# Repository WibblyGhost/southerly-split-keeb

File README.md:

# The Southerly - Split Keeb

**Brrrr is it cold down here in New Zealand winters!**

## Intro

In 2024 I was getting some serious wrist pain issues from typing all day at my job as a programmer, so I ventured into the world of split keyboards.

Initially I was just curious, but as time went on I really enjoyed the idea of having two keyboard halves an was quite keen on the staggered column. This quickly turned into a purchase of my first split keyboard, the [ZSA Voyager](https://www.zsa.io/voyager). I quickly fell in love with the keyboard and how it felt with my hands.
Alongside also purchasing a Logitech MX Ergo trackball mouse.

I had quite a tough learning experience to switching to the Voyager strictly due to the fact that whilst I changed keyboard layouts, I switched from traditional mice to trackball mice, **and** started learning the ColemakDH keyboard layout.

Switching to the new layer system, getting rid of the numpad, F-keys, moving spaces, tabs and enters; whilst incredibly fun, was quite intensive switch over. But now sitting here a few months after my mission to improve desk ergonomics; I'm feeling a hell of a lot better with all my pain, voila, gone!

## Layout Printouts/Design - ErgoGen

I came across ErgoGen when researching about split keyboards, this piece of software is marvelous... complex but marvelous. It took me quite a while to figure out how to use ErgoGen and their official docs are still a WIP meaning I was initially going blind with this software.

I came across this youtube video [ErgoGen Tutorial](https://www.youtube.com/watch?v=7UXsD7nSfDY) which dramatically helped me start with the design of my keyboard.

Another great guide I came across was this one, which in my honest opinion, **is the best ErgoGen doc set I have found to date**; [ErgoGen Full Guide](https://flatfootfox.com/ergogen-part1-units-points/)

As an initial design process I decided to create a few models, drill holes and tried them out on my fingers. With my owned Voyager, I was able to replicate quite easily the positioning I wanted all the keys in, with the addition of a couple more thumb keys.

There was going to be three layers to the case design which I'll get into later. But the brief is a bottom plate which becomes the surrounding case, a top plate which sits just under the switches (they click into the top layer) and the circuit board which will be centered below the top layer by a few millimeters.

### Prototyping

I made **lots** of prototypes for my board as I went through multiple designs. Starting with a basic layout to see what worked well with my hands with the original Voyager as reference.

## PCB Design - KiCad

Once I sorted out the prototyping of the board I moved on to the wiring of the circuit board. The PCB was designed with the idea of being reversible, meaning you can mount the components either way, *but there was a caveat there*.

The PCB design was fairly straightforward running the horizontal traces on one layer and vertical traces on the other, with an addition of two ground planes and thicker VCC/GND traces. The only annoying thing was that KiCad, for the life of me, doesn't support angle snapping at strange angles; and my thumb cluster is on a 30° angle. Making the thumb cluster super messy. Sigh...

The RGB data in and data out connectors were not a part of the schematic so I had to use a third party plugin to help me modify the web and attach the string of LED's to one of the PCB's pinouts. [WireIt](https://github.com/devbisme/WireIt)

After designing the PCB I shipped the Gerber off to JLCPBC to print off for me.

### PCB Underside - LH

### PCB Topside - LH

## Gotcha Moment

Although once receiving the board I realized that the reversible board wouldn't work with the ProMicro the way I had designed it for the 3D design plan as I wanted a minimal keyboard with little height. For that I would have needed to mount MCU directly on the circuit board. So that's a consideration for my next build.

Since my board was already designed to be flippable, the only thing I needed to change was the MCU, so I flipped the MCU footprint and re-traced everything again for the right handed layout.

### PCB Underside - RH

### PCB Topside - RH

## Case Design - AutoDesk Fusion

Whilst ErgoGen can and does generate most 3D print designs and DXF files, I found it quite fiddly changing the YAML constantly to design a case.

So instead I decided that the best course was to get a rough outline in ErgoGen, then work the rest of the design in AutoDesk. The ErgoGen created some annoying fillets in the output, so I removed those and re-created the fillets to clean up the design.

### Upper Case

This was fairly straightforward as I just imported the base outlines created from ErgoGen as sketches and worked on them from there.

From the sketches I firstly designed the upper case which was designed to clip into a base.

Using the sketch outputs I was able to create the Choc V1 socket holes, added key cap pullers to them, and a rectangular cutout underneath to allow the switched to clip into the case properly.

The addition of the reset switch, TRRS and USB-C cutouts was straightforward, just an easy sketch and a subtraction extrude.

Additional fun logo was embossed onto the case too.

> [!NOTE]
> Total thickness of the area between the top plate and rectangular cutout must be exactly 14mm for the switches to properly click in, this was giving me some grief with our 3D printer, we set infill to 100% to prevent any wavey patterns around the switches, and waited until the 3D print bed completely cooled. Otherwise the switch holes shrunk due to rapid cooling or warping.
>
> Also, the TRRS cutout needed a 'brim ears' underneath to prevent liftoff from the base plate during printing.

### Lower Case

From the sketches I designed a lower case, or base, which will support an upper case and fit snugly together. This was done by creating inner walls which extruded into the top layer *(subtraction)* to the fit, and a hex fill for supporting the PCB, *which I also added some foam in for sound proofing and support*.

Adding in a patterned hex structure to the inside to help support the PCB. I added some foam on top of this to fill in the spaces, provide more support, and sound proofing.

### Standoffs

I made some simple standoff feet to tent the keyboard and am using rubber to help prevent the keyboard from moving on the desk. It can be attached via a M5 screw and washer pair and the rubber layer either glued of clipped into the standoff base. I used PLA for the base of the standoff and TPU rubber for the foot.

### Combined Output

## QMK Firmware

QMK was an interesting beast to try learn and it took me a lot of trial and error figuring out how to program the keyboard. I'm still confused on what the right way to define the parameters are, we have the legacy solution, C header files, C files and rules makefiles, or data driven files with JSON which is the new format. However the documentation isn't really up to date with the new JSON format and the C files also lacked up to date documentation.

There were other keyboards in the repository that I had to copy and paste to see what worked and what didn't.

The pinouts of the ProMicro was a bit confusing at first as they didn't match what was on the MCU physically; once I found this image I was able to map the pins correctly to the PCB design. Now correctly mapping the columns and rows, and RGB matrix.

Also found it quite handy that I was able to download the source QMK firmware for the Voyager and reverse engineer the QMK setup for the Voyager. This allowed me to understand the QMK design process better and how the matrices are used. Also means that I could take a layout I made for my Voyager and with the addition of the extra thumb buttons and removal of some unnecessary functions, was able to get a running board very quickly.

## Components

| Components | ID | Links | Total Cost (NZD) | Quantity | Notes |
| ---------- | -- | ----- | ---------- | -------- | ----- |
| Choc V1 Keycaps | | [Tai-Hao Thins](https://shop.tai-hao.com/products/white-1) | $96.67 | | Same key caps as ZSA Voyager (Needs to be double injected for the RGB) |
| Choc V1 Switches | | [Robins](https://keebd.com/en-nz/products/ambients-silent-linear-twilight-choc-switches?_pos=2&_fid=9a770a5f9&_ss=c) | $60 | 60 | |
| Kailh Hotswap Sockets | | [Choc Hotswap Sockets](https://www.aliexpress.com/item/1005006833673668.html) | $24 | 60 | |
| Pico Micro (USB-C) | | [AliExpress](https://www.aliexpress.com/item/1576902211.html) | $13.7 | 2 | |
| Surface Mount Diodes | SOD 123 - DSF1J | [LCSC](https://www.lcsc.com/product-detail/Fast-Recovery-High-Efficiency-Diodes_FUXINSEMI-DSF1J_C915615.html) | $1.58 | 200 | |
| RGB | led_sk6812mini-e | [LCSC](https://www.lcsc.com/product-detail/RGB-LEDs-Built-in-IC_OPSCO-Optoelectronics-SK6812MINI-E_C5149201.html) | $7.15 | 100 | |
| Surface Mount Reset Button | EVQPUA02K | [LCSC](https://www.lcsc.com/product-detail/Tactile-Switches_PANASONIC-EVQPUA02K_C128539.html) | $1.62 | 5 | |
| TRRS Connector | PJ-320A | [LCSC](https://www.lcsc.com/product-detail/Audio-Connectors_XKB-Connectivity-PJ-320AG-B_C2884984.html) | $0.39 | 5 | |
| TRRS Cable | UGREEN 20782 | [PB Tech](https://www.pbtech.co.nz/product/CABUGR6192/UGREEN-20782-35mm-Male-To-Male-Cable---2M) | $20 | 5 | **You need a 4 pole TRRS cable** (I struggled finding one so just ordered one locally) |
| Circuit Board | | [JLCPCB](https://jlcpcb.com/) | $11.76 | 5 | |
| **Total** | | | **$236.87** | | |

## Notes

- The key caps **must** be double injected for the RGB to shine through, otherwise you will just get an under-glow.

### ErgoGen

- [ErgoGen Guide - Units & Points](https://flatfootfox.com/ergogen-part1-units-points/)
- [YouTube Guide - Designing and Building a Split Keyboard](https://www.youtube.com/watch?v=7UXsD7nSfDY)
- [Notion Guide - Convert KiCad to ErgoGen Footprints](https://nilnil.notion.site/Convert-Kicad-Footprints-to-Ergogen-8340ce87ad554c69af4e3f92bc9a0898)
- [ErgoGen Footprints](https://github.com/ceoloide/ergogen-footprints/tree/main)

### PCB

- [PCB Addon - Wire RatsNest](https://github.com/devbisme/WireIt)
- [PCB Printing - JLCPCB](https://jlcpcb.com/)

### QMK

- [QMK Bootloader](https://docs.qmk.fm/driver_installation_zadig#list-of-known-bootloaders)
- [QMK Matrix to Physical Layout Map](https://docs.qmk.fm/understanding_qmk#matrix-to-physical-layout-map)
- [VSCode Setup](https://docs.qmk.fm/other_vscode)
- Split Keyboard
  - [Serial Wiring](https://docs.qmk.fm/features/split_keyboard#serial-wiring)
  - [Split Keyboard](https://docs.qmk.fm/features/split_keyboard#split-keyboard)
  - [Keeb Handedness](https://docs.qmk.fm/features/split_keyboard#handedness-by-eeprom)
- RGB
  - [RGB: WS2812 LED](https://docs.qmk.fm/drivers/ws2812)
  - [RGB: Matrix](https://docs.qmk.fm/features/rgb_matrix)
- TRRS
  - [TRRS: I2C](https://docs.qmk.fm/drivers/i2c)
  - [TRRS: Serial](https://docs.qmk.fm/drivers/serial)
- Data Driven Configs (.json) - New
  - [QMK JSON (.json) - Preferred Way](https://docs.qmk.fm/reference_info_json)
  - [QMK Data Driven Config](https://docs.qmk.fm/data_driven_config)
- Header Configs (.h/.mk) - Legacy
  - [QMK Config.h](https://docs.qmk.fm/config_options#the-configh-file)
  - [QMK Rules.mk](https://docs.qmk.fm/config_options#the-rules-mk-file)

<!-- TODO: qmk flash -kb southerly -km default -bl avsdude-split-left -->

## Improvements & Considerations

- Next time instead of using a Pro Micro, I will use a MEGA32U4 directly on the board and design the components directly into the board.
  > This will cleanup the USB-C port location and make the reversible board work correctly without having to re-design the PCB case for the mirrored side.

- Diagnose why a TRRS port isn't compatible with a TRS cable *(common audio cable)*, it must use a TRRS cable instead *(4 Pole audio cable)*.
  > I had troubles when first trying this out with a TRS cable and it shorted VCC to GND, the MCU never booted whilst plugged into TRRS.

- Use I2C for TRRS communications next time, this requires some rewiring on the PCB with some pull up resistors. But will allow for multiple devices to be connected through TRRS.

- Figure out how to do matrix lighting from master to slave. (It's doesn't seem to want to update the slave correctly)

- Figure out how the master slave connection works properly, allow USB connection from either side?

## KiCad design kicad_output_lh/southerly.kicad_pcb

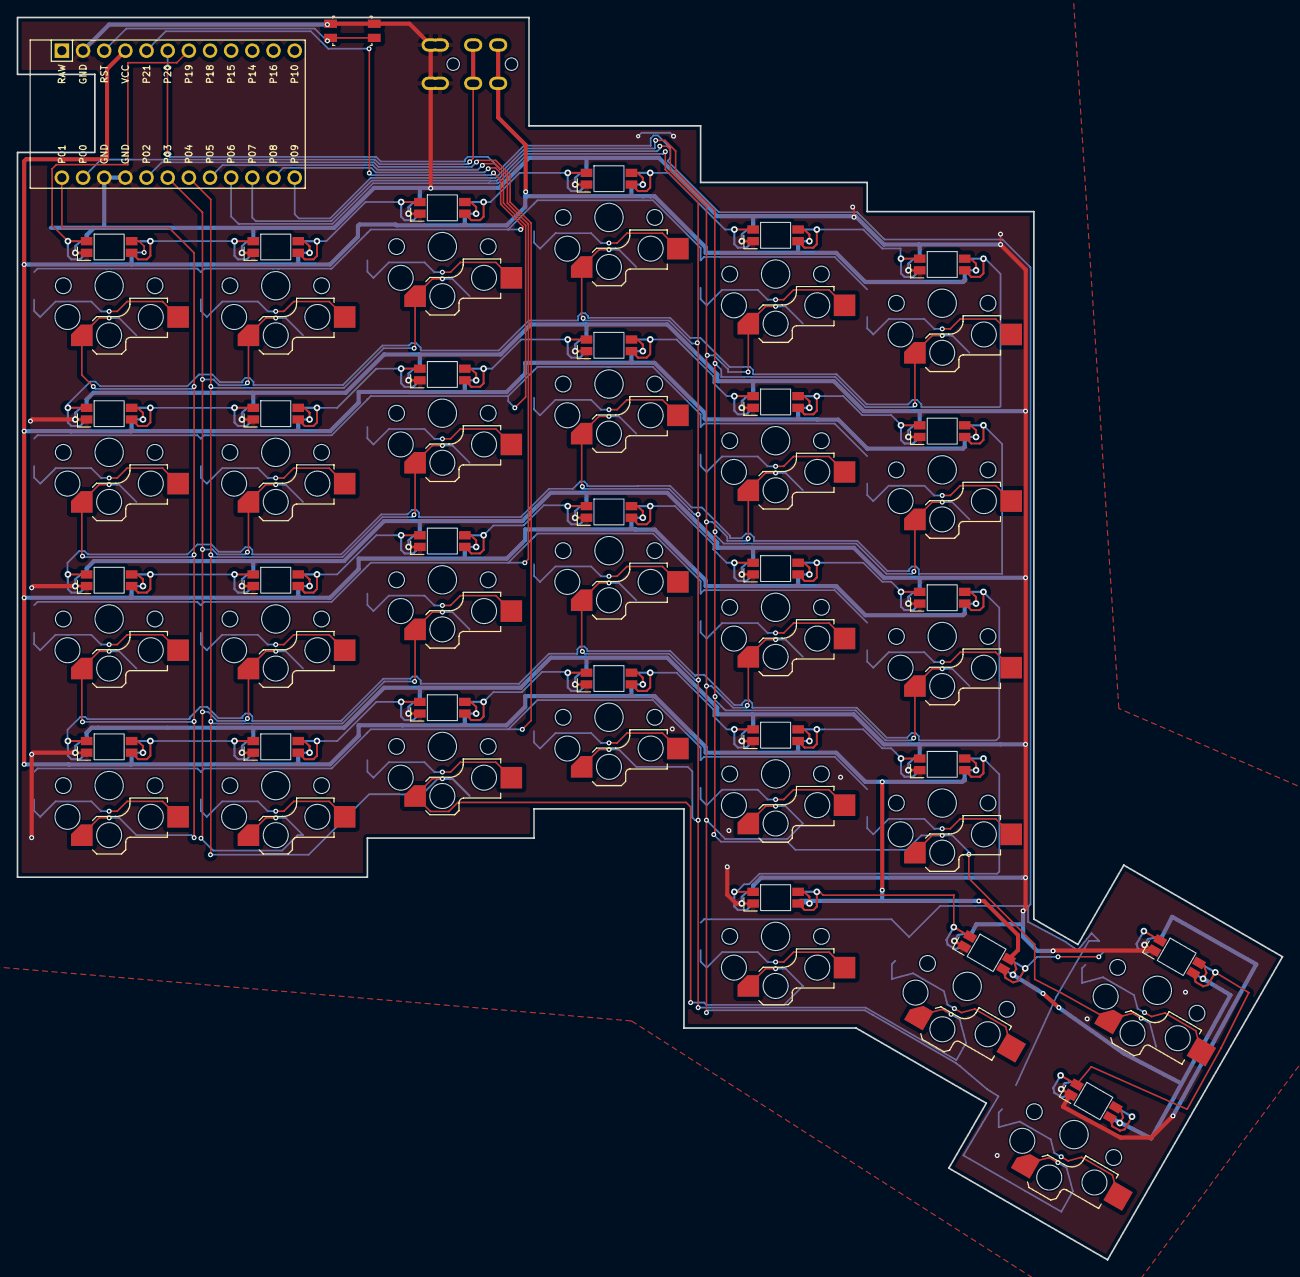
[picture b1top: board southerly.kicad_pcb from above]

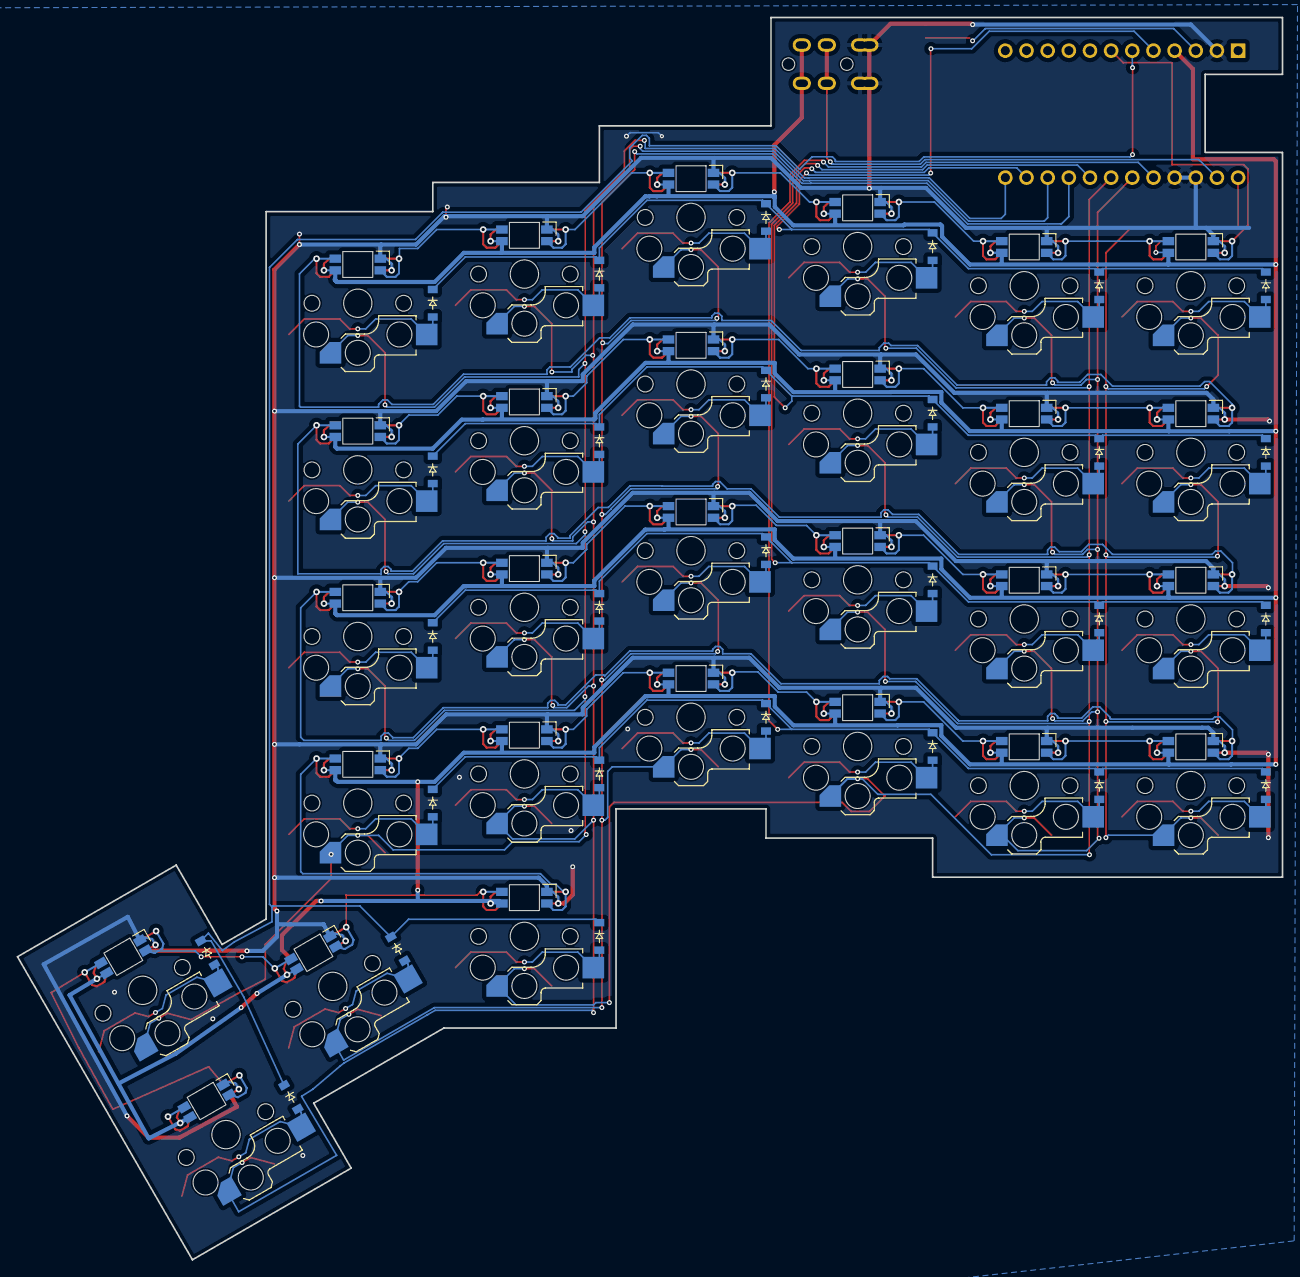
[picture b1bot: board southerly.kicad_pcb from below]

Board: 2 copper layers, 151.8 x 149.1 mm, 87 parts (84 on the bottom side), 71 nets.

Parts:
D1, D2, D3, D4, D5, D6, D7, D8, D9, D10, D11, D12, D13, D14, D15, D16, D17, D18, D19, D20, D21, D22, D23, D24, D25, D26, D27, D28: diode_tht_sod123
LED1, LED2, LED3, LED4, LED5, LED6, LED7, LED8, LED9, LED10, LED11, LED12, LED13, LED14, LED15, LED16, LED17, LED18, LED19, LED20, LED21, LED22, LED23, LED24, LED25, LED26, LED27, LED28: led_SK6812mini-e (per-key, reversible)
MCU1: ProMicro
RST1: reset_switch_smd_side
S1, S2, S3, S4, S5, S6, S7, S8, S9, S10, S11, S12, S13, S14, S15, S16, S17, S18, S19, S20, S21, S22, S23, S24, S25, S26, S27, S28: switch_choc_v1_v2
TRRS1: TRRS-PJ-320A-dual

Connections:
GND: LED1.3, LED2.3, LED3.3, LED4.3, LED5.3, LED6.3, LED7.3, LED8.3, LED9.3, LED10.3, LED11.3, LED12.3, LED13.3, LED14.3, LED15.3, LED16.3, LED17.3, LED18.3, LED19.3, LED20.3, LED21.3, LED22.3, LED23.3, LED24.3, LED25.3, LED26.3, LED27.3, LED28.3, MCU1.2, MCU1.15, MCU1.16, RST1.1, RST1.3, TRRS1.1, TRRS1.2
P0: MCU1.14, TRRS1.3
P1: MCU1.13, S1.1, S2.1, S3.1, S4.1
P2: D1.1, D5.1, D9.1, D13.1, D17.1, D21.1, MCU1.17
P3: MCU1.18, S5.1, S6.1, S7.1, S8.1
P4: MCU1.19, S9.1, S10.1, S11.1, S12.1, S25.1
P5: D2.1, D6.1, D10.1, D14.1, D18.1, D22.1, MCU1.20
P6: MCU1.21, S13.1, S14.1, S15.1, S16.1, S26.1
P7: MCU1.22, S17.1, S18.1, S19.1, S20.1, S27.1
P8: D3.1, D7.1, D11.1, D15.1, D19.1, D23.1, MCU1.23
P9: MCU1.24, S21.1, S22.1, S23.1, S24.1, S28.1
P19: LED4.4, MCU1.7
P20: D25.1, D26.1, D27.1, D28.1, MCU1.6
P21: D4.1, D8.1, D12.1, D16.1, D20.1, D24.1, MCU1.5
RST: MCU1.3, RST1.2, RST1.4
VCC: LED1.1, LED2.1, LED3.1, LED4.1, LED5.1, LED6.1, LED7.1, LED8.1, LED9.1, LED10.1, LED11.1, LED12.1, LED13.1, LED14.1, LED15.1, LED16.1, LED17.1, LED18.1, LED19.1, LED20.1, LED21.1, LED22.1, LED23.1, LED24.1, LED25.1, LED26.1, LED27.1, LED28.1, MCU1.4, TRRS1.4
di_index_bottom: LED13.2, LED17.4
di_index_home: LED14.2, LED18.4
di_index_num: LED16.2, LED20.4
di_index_top: LED15.2, LED19.4
di_inner_bottom: LED17.2, LED21.4
di_inner_home: LED18.2, LED22.4
di_inner_num: LED20.2, LED24.4
di_inner_top: LED19.2, LED23.4
di_middle_bottom: LED9.2, LED13.4
di_middle_home: LED10.2, LED14.4
di_middle_num: LED12.2, LED16.4
di_middle_top: LED11.2, LED15.4
di_outer_bottom: LED1.4, LED22.2
di_outer_home: LED2.4, LED23.2
di_outer_top: LED3.4, LED24.2
di_pinkey_bottom: LED1.2, LED5.4
di_pinkey_home: LED2.2, LED6.4
di_pinkey_top: LED3.2, LED7.4
di_ring_bottom: LED5.2, LED9.4
di_ring_home: LED6.2, LED10.4
di_ring_num: LED8.2, LED12.4
di_ring_top: LED7.2, LED11.4
di_thumb_left_key: LED21.2, LED25.4
di_thumb_middle_key: LED25.2, LED26.4
do_outer_num: LED4.2, LED8.4
do_thumb_middle_key: LED26.2, LED28.4
do_thumb_top_key: LED27.4, LED28.2
index_bottom: D17.2, S17.2
index_home: D18.2, S18.2
index_num: D20.2, S20.2
index_top: D19.2, S19.2
inner_bottom: D21.2, S21.2
inner_home: D22.2, S22.2
inner_num: D24.2, S24.2
inner_top: D23.2, S23.2
middle_bottom: D13.2, S13.2
middle_home: D14.2, S14.2
middle_num: D16.2, S16.2
middle_top: D15.2, S15.2
outer_bottom: D1.2, S1.2
outer_home: D2.2, S2.2
outer_num: D4.2, S4.2
outer_top: D3.2, S3.2
pinkey_bottom: D5.2, S5.2
pinkey_home: D6.2, S6.2
pinkey_num: D8.2, S8.2
pinkey_top: D7.2, S7.2
ring_bottom: D9.2, S9.2
ring_home: D10.2, S10.2
ring_num: D12.2, S12.2
ring_top: D11.2, S11.2
thumb_left_key: D25.2, S25.2
thumb_middle_key: D26.2, S26.2
thumb_right_key: D27.2, S27.2
thumb_top_key: D28.2, S28.2

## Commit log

2024-12-05 Add new keyboard layout for ergogen
2024-12-08 Updated configs, added images and created README
2024-12-21 Update README and add more design images
2025-01-09 Update KiCad drawings and add STL output files
2025-01-14 Add basic working QMK firmware
2025-01-14 Update notes.txt with QMK information
2025-01-29 Update project with new step files, images and readme
2025-02-10 Basic working QMK setup
2025-03-07 Update QMK keymapping
2025-03-16 Updated key mappings
2025-03-16 Naming issue for layout
2025-03-22 Added standoff feet
